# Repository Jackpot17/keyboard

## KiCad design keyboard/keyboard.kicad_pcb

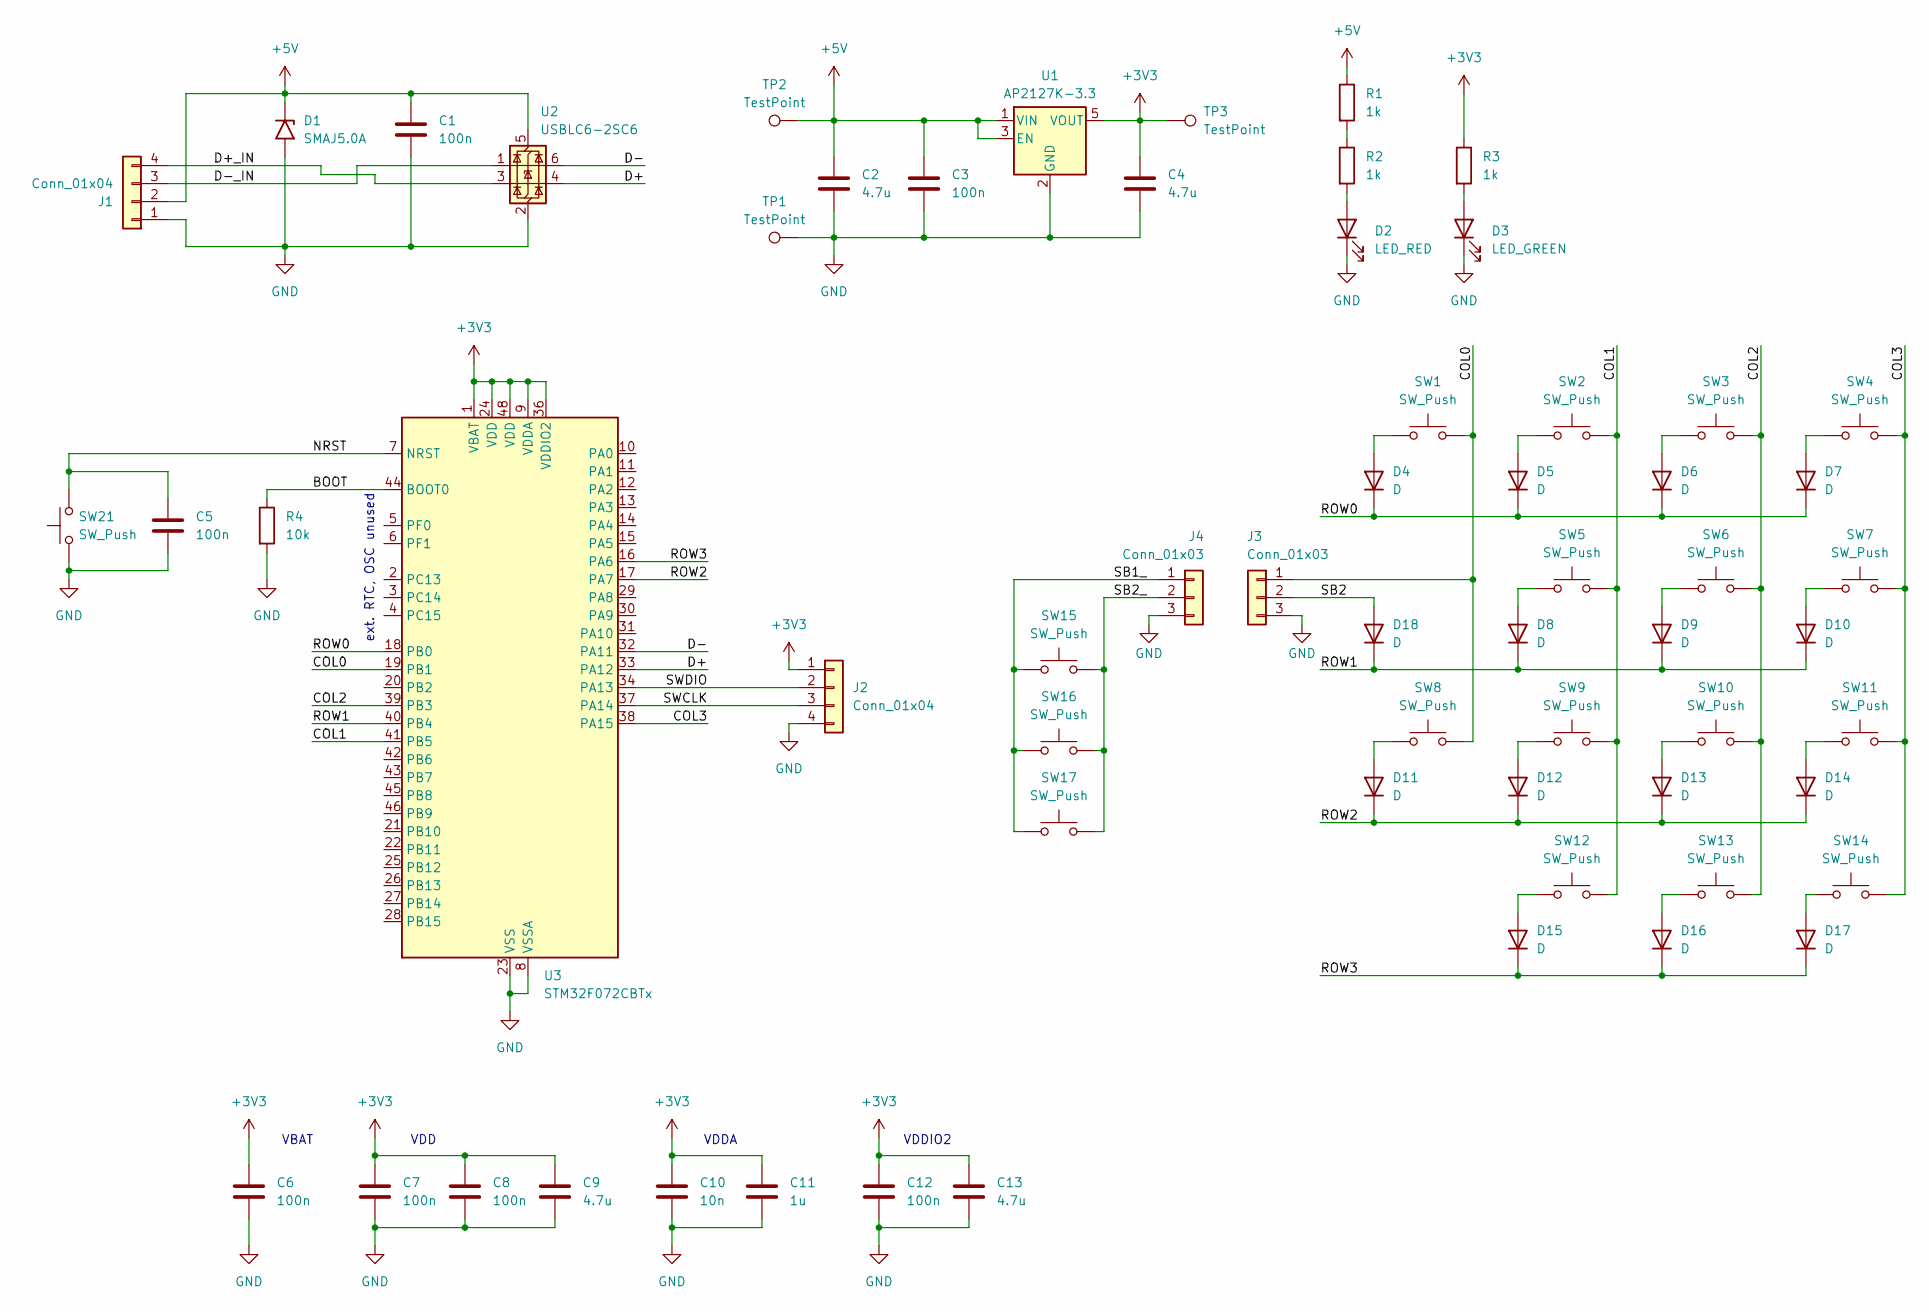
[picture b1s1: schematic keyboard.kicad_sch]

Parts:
C1, C3, C5, C6, C7, C8, C12: 100n; C_0603_1608Metric
C2, C4: 4.7u; C_0805_2012Metric
C9, C13: 4.7u; C_0603_1608Metric
C10: 10n; C_0603_1608Metric
C11: 1u; C_0603_1608Metric
D1: SMAJ5.0A; D_SMA
D2: LED_RED; LED_0603_1608Metric
D3: LED_GREEN; LED_0603_1608Metric
D4, D5, D6, D7, D8, D9, D10, D11, D12, D13, D14, D15, D16, D17, D18: D; D_SOD-323
J1: Conn_01x04
J2: Conn_01x04; PinHeader_1x04_P1.27mm_Vertical
J3, J4: Conn_01x03
R1, R2, R3: 1k; R_0603_1608Metric
R4: 10k; R_0603_1608Metric
SW1, SW2, SW3, SW4, SW5, SW6, SW7, SW8, SW9, SW10, SW11, SW12, SW13, SW14, SW15, SW16, SW17: SW_Push; SW_MX_HS_KS-2P02B01-01_1.5u
SW21: SW_Push; SW_SPST_TL3305A
TP1, TP2, TP3: TestPoint; TestPoint_Pad_D1.0mm
U1: AP2127K-3.3; SOT-23-5
U2: USBLC6-2SC6; SOT-23-6
U3: STM32F072CBTx; LQFP-48_7x7mm_P0.5mm

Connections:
+3V3: C4.1, C6.1, C7.1, C8.1, C9.1, C10.1, C11.1, C12.1, C13.1, J2.1, R3.1, TP3.1 (1_1), U1.5 (VOUT), U3.1 (VBAT), U3.9 (VDDA), U3.24 (VDD), U3.36 (VDDIO2), U3.48 (VDD)
+5V: C1.1, C2.1, C3.1, D1.1 (A1), J1.2, R1.1, TP2.1 (1_1), U1.1 (VIN), U1.3 (EN), U2.5 (VBUS); also elsewhere on the board
/BOOT: R4.1, U3.44 (BOOT0)
/COL0: J3.1, SW1.2, SW8.2, U3.19 (PB1); also elsewhere on the board
/COL1: SW2.2, SW5.2, SW9.2, SW12.2, U3.41 (PB5)
/COL2: SW3.2, SW6.2, SW10.2, SW13.2, U3.39 (PB3)
/COL3: SW4.2, SW7.2, SW11.2, SW14.2, U3.38 (PA15)
/D+: U2.4 (I/O2), U3.33 (PA12)
/D+_IN: J1.4, U2.3 (I/O2); also elsewhere on the board
/D-: U2.6 (I/O1), U3.32 (PA11)
/D-_IN: J1.3, U2.1 (I/O1); also elsewhere on the board
/NRST: C5.1, SW21.2, U3.7 (NRST)
/ROW0: D4.1 (K), D5.1 (K), D6.1 (K), D7.1 (K), U3.18 (PB0)
/ROW1: D8.1 (K), D9.1 (K), D10.1 (K), D18.1 (K), U3.40 (PB4)
/ROW2: D11.1 (K), D12.1 (K), D13.1 (K), D14.1 (K), U3.17 (PA7)
/ROW3: D15.1 (K), D16.1 (K), D17.1 (K), U3.16 (PA6)
/SB1_: J4.1, SW15.1, SW16.1, SW17.1; also elsewhere on the board
/SB2: D18.2 (A), J3.2; also elsewhere on the board
/SB2_: J4.2, SW15.2, SW16.2, SW17.2; also elsewhere on the board
/SWCLK: J2.3, U3.37 (PA14)
/SWDIO: J2.2, U3.34 (PA13)
GND: C1.2, C2.2, C3.2, C4.2, C5.2, C6.2, C7.2, C8.2, C9.2, C10.2, C11.2, C12.2, C13.2, D1.2 (A2), D2.1 (K), D3.1 (K), J1.1, J2.4, J3.3, J4.3, R4.2, SW21.1, TP1.1 (1_1), U1.2 (GND), U2.2 (GND), U3.8 (VSSA), U3.23 (VSS), U3.35 (VSS), U3.47 (VSS); also elsewhere on the board
unnamed: D2.2 (A), R2.2
unnamed: D3.2 (A), R3.2
unnamed: D4.2 (A), SW1.1
unnamed: D5.2 (A), SW2.1
unnamed: D6.2 (A), SW3.1
unnamed: D7.2 (A), SW4.1
unnamed: D8.2 (A), SW5.1
unnamed: D9.2 (A), SW6.1
unnamed: D10.2 (A), SW7.1
unnamed: D11.2 (A), SW8.1
unnamed: D12.2 (A), SW9.1
unnamed: D13.2 (A), SW10.1
unnamed: D14.2 (A), SW11.1
unnamed: D15.2 (A), SW12.1
unnamed: D16.2 (A), SW13.1
unnamed: D17.2 (A), SW14.1
unnamed: R1.2, R2.1

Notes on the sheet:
ext. RTC, OSC unused
VDD
VBAT
VDDA
VDDIO2

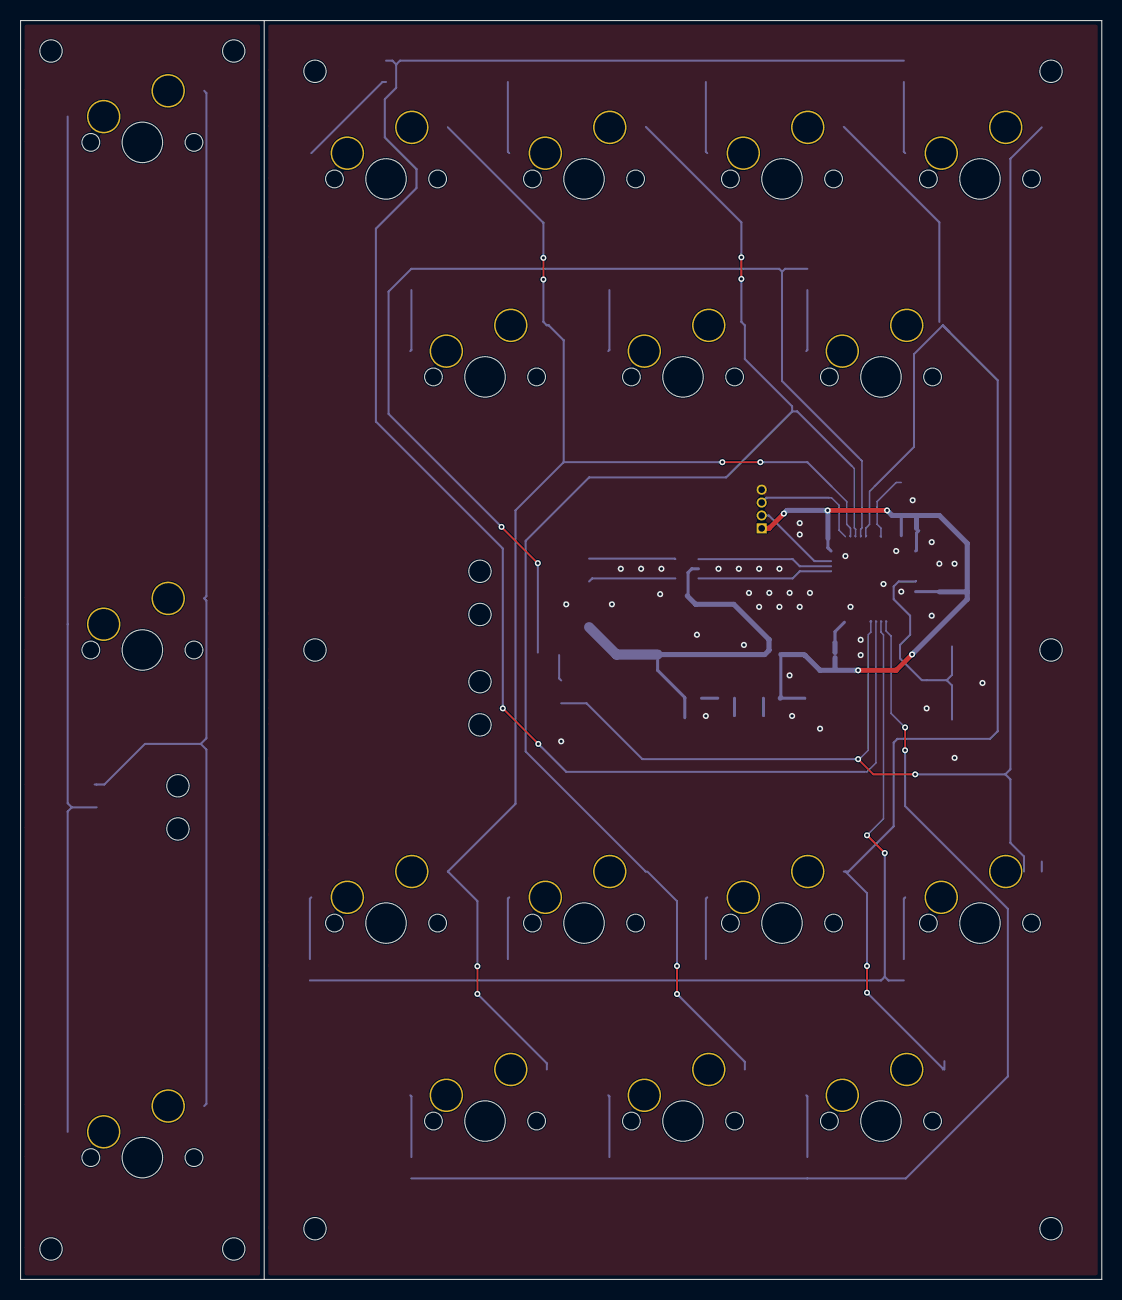
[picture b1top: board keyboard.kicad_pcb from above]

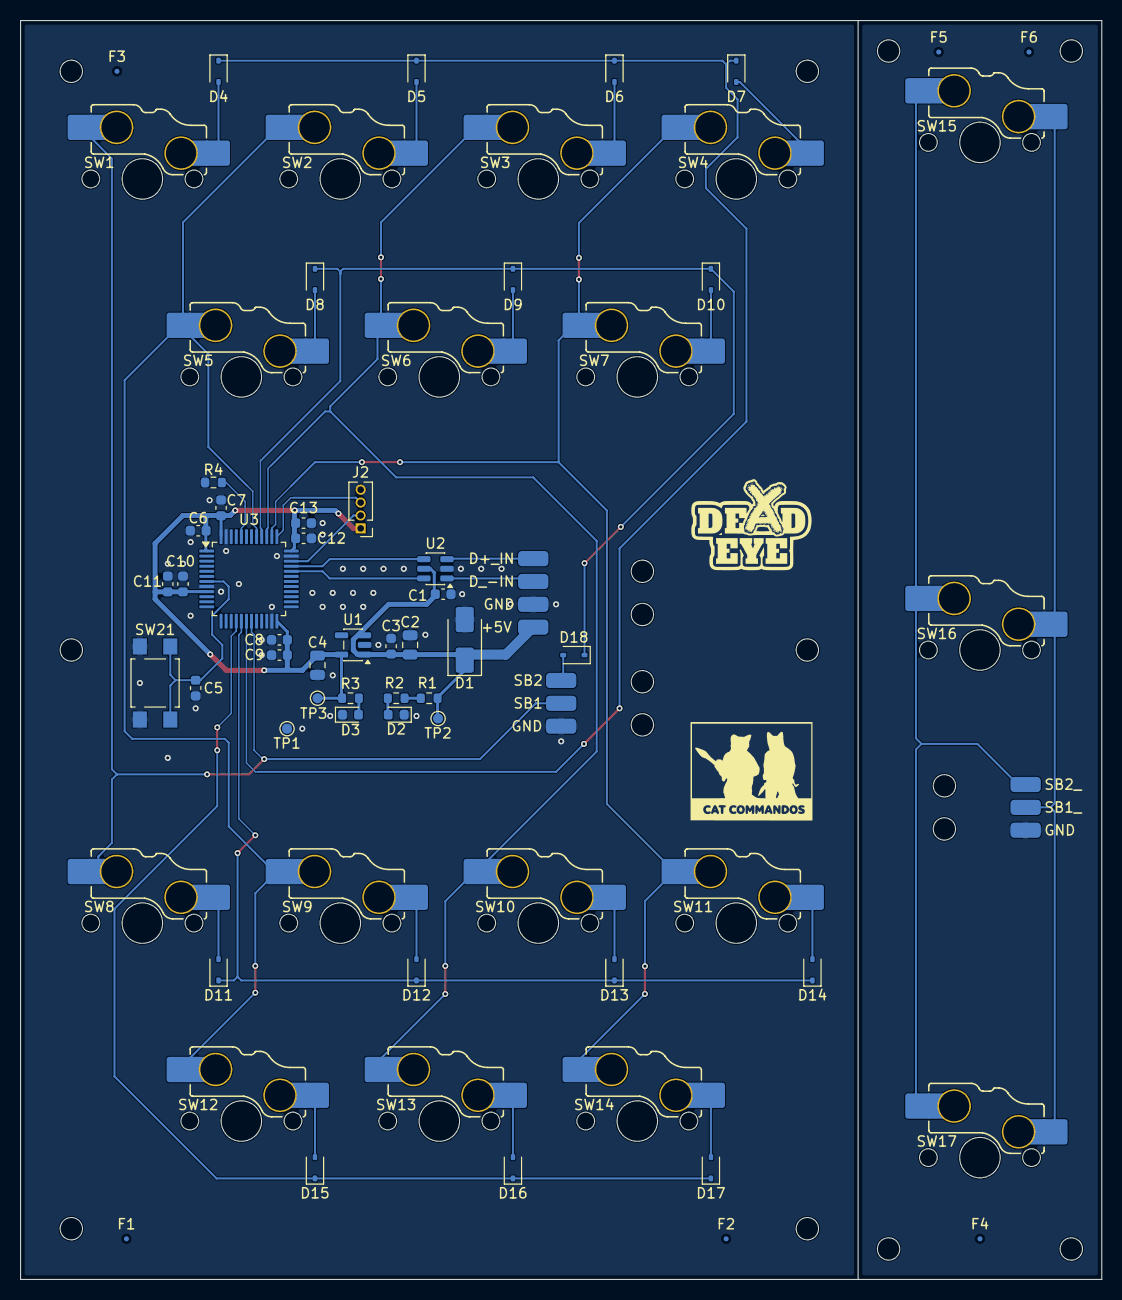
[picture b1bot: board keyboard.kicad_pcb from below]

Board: 2 copper layers, 106.5 x 124.0 mm, 76 parts (76 on the bottom side), 39 nets.

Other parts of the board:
+5V: SolderWirePad_1x01_SMD_1.5x3mm
D+_IN: SolderWirePad_1x01_SMD_1.5x3mm
D_-IN: SolderWirePad_1x01_SMD_1.5x3mm
F1, F2, F3, F4, F5, F6: Fiducial_0.5mm_Mask1mm
GND: SolderWirePad_1x01_SMD_1.5x3mm
GND#2, GND#3: SolderWirePad_1x01_SMD_1.5x3mm
SB1, SB1_, SB2, SB2_: SolderWirePad_1x01_SMD_1.5x3mm

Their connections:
+5V: +5V.1; also elsewhere on the board
/COL0: SB1.6; also elsewhere on the board
/D+_IN: D+_IN.4; also elsewhere on the board
/D-_IN: D_-IN.3; also elsewhere on the board
/SB1_: SB1_.9; also elsewhere on the board
/SB2: SB2.7; also elsewhere on the board
/SB2_: SB2_.10; also elsewhere on the board
GND: GND.5, GND#2.2, GND#3.8; also elsewhere on the board

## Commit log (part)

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2026-05-11 Schematic complete, initial component placement on PCB. Not reviewed.
2026-05-14 Key layout according to TB drawing.
2026-05-15 Added board outlines 12mm from key switch centres.
2026-05-15 Added connector cutout and V-groove for cut. Moved dimensions onto user drawings layer.
2026-05-15 Some mounting holes.
2026-05-18 Some switch traces.
2026-06-05 Some routing.
